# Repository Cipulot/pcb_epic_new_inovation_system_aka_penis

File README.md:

# pcb_epic_new_inovation_system_aka_penis
Do NOT use this in any comercial way ,all the files may not be used to gain any profit. Retail of these designs is not allowed by anyone else then the creator. Also dont complain about the PCB.

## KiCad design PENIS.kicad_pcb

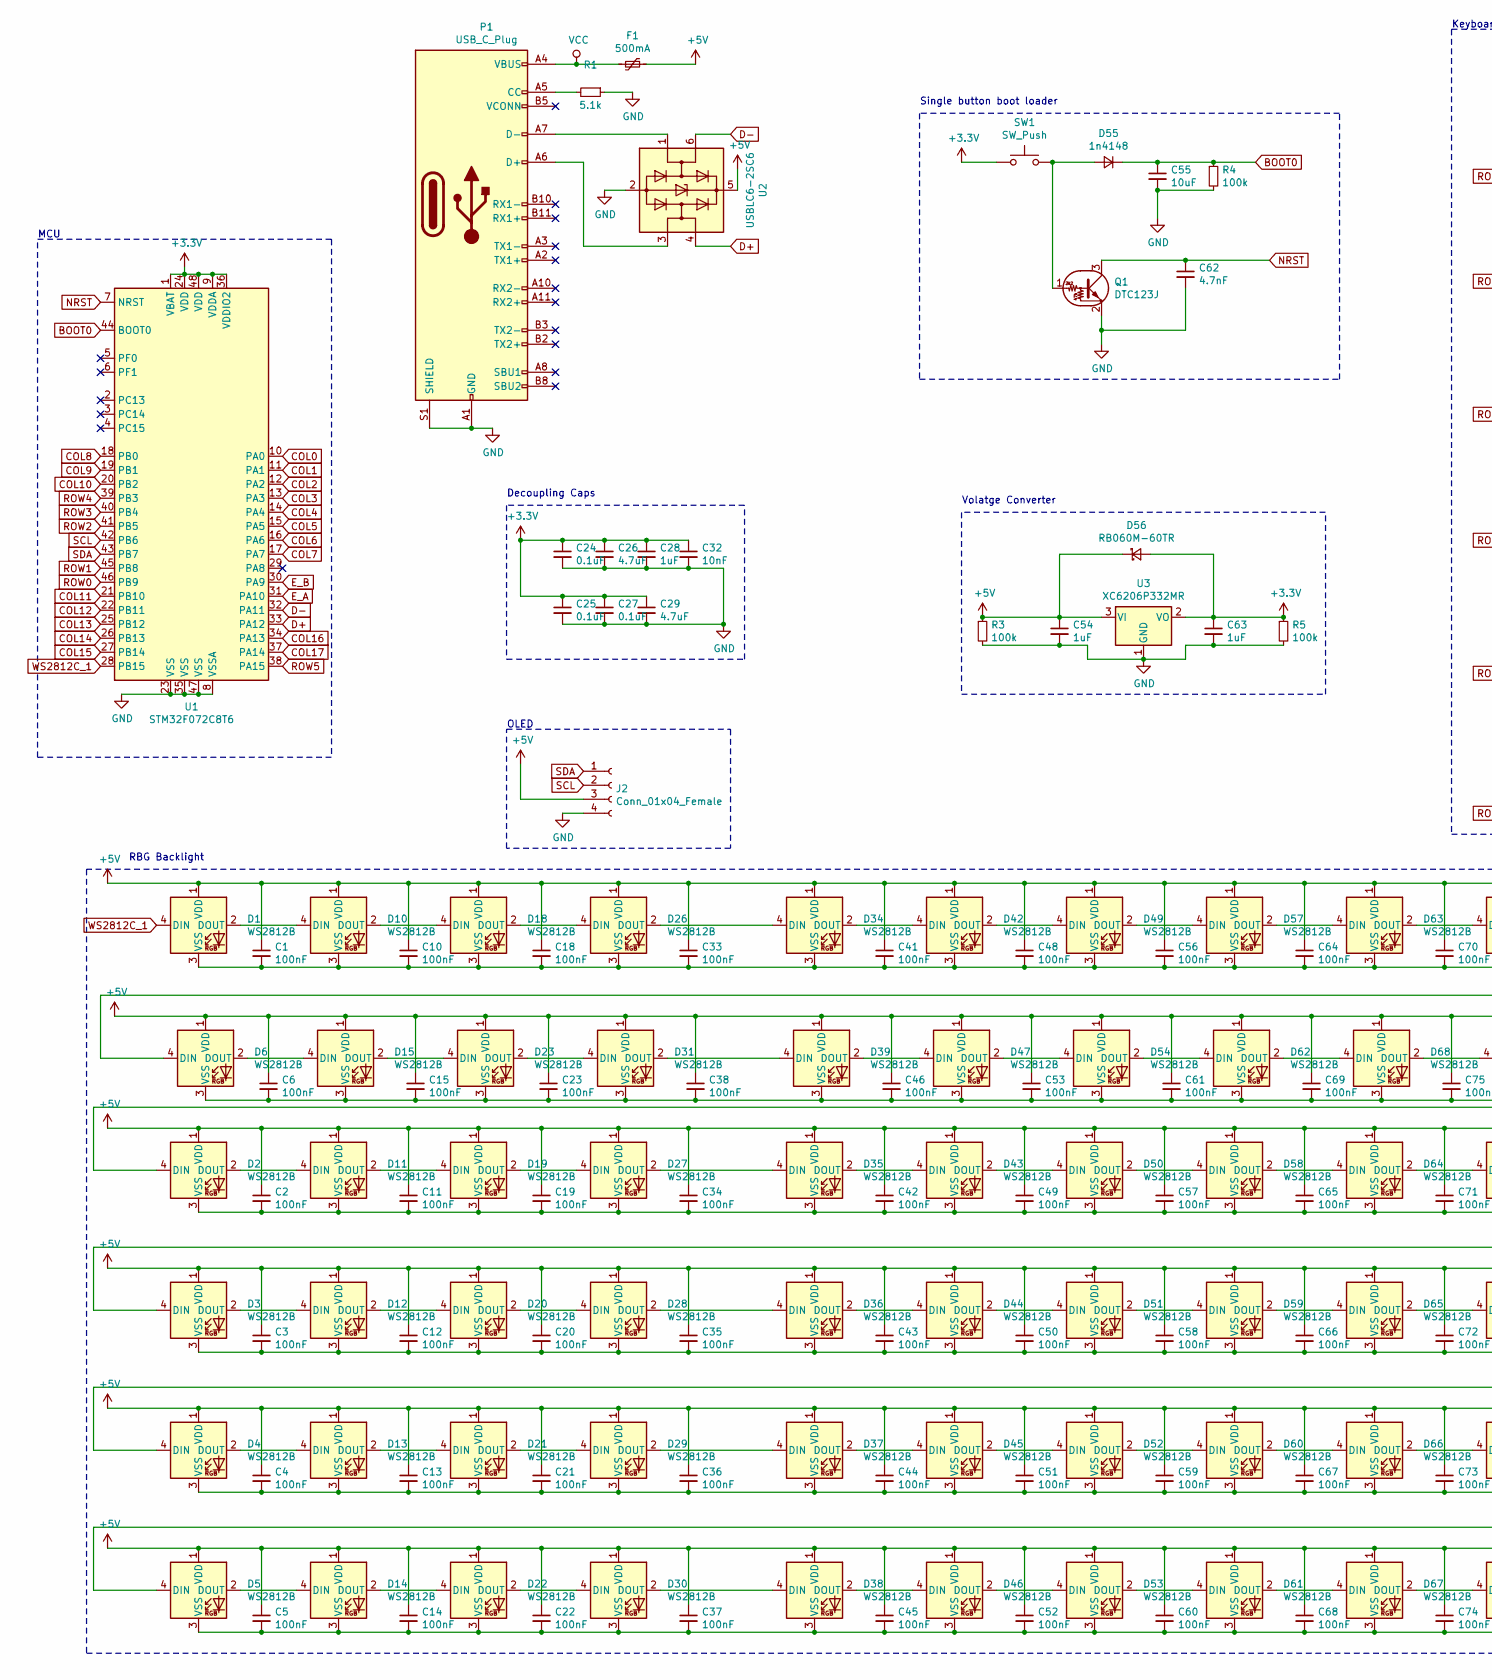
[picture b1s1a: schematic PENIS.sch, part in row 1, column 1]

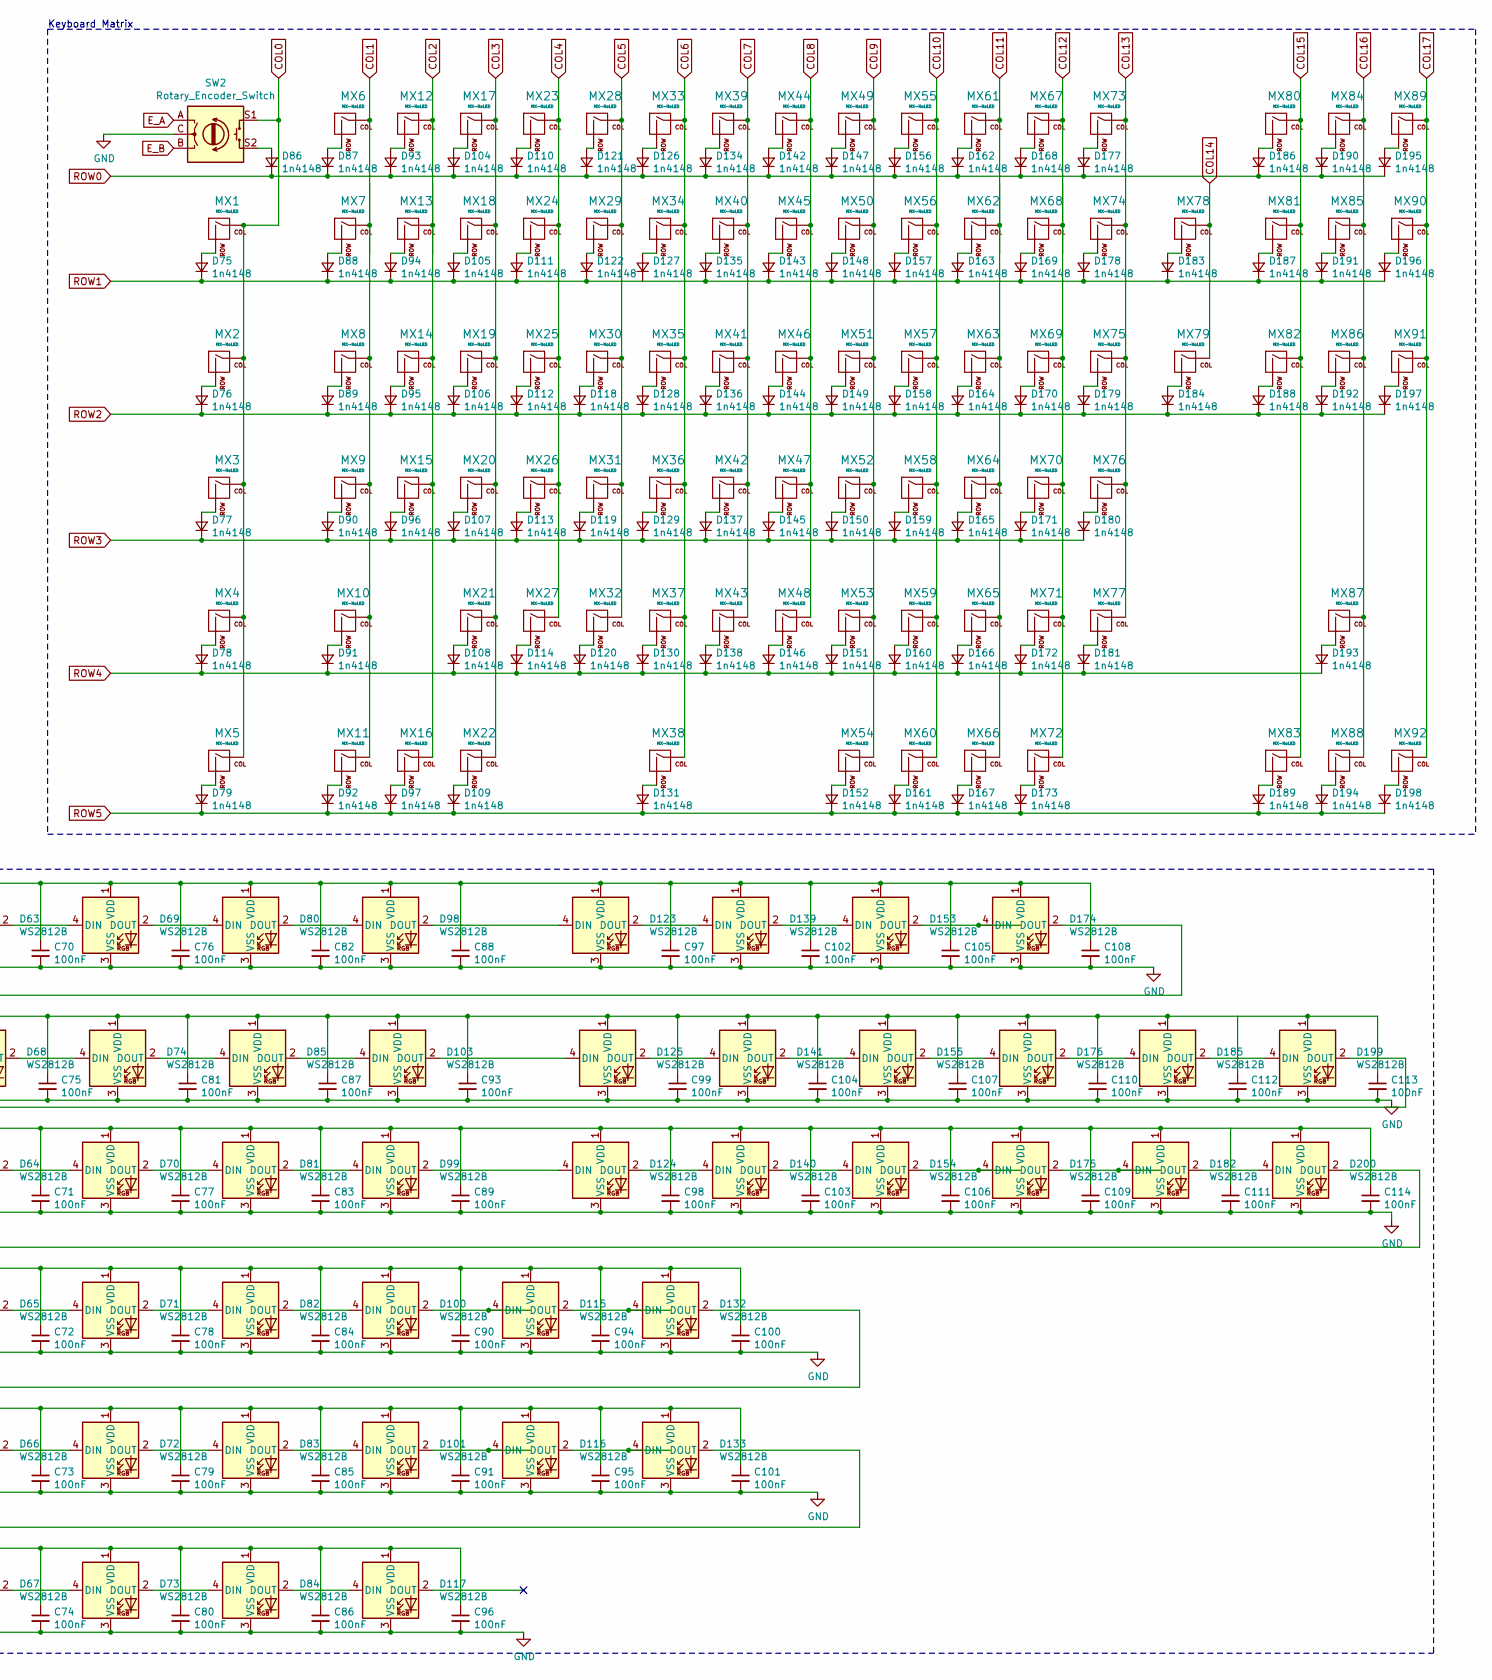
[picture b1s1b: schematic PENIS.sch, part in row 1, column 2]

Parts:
C1, C2, C3, C4, C5, C6, C10, C11, C12, C13, C14, C15, C18, C19, C20, C21, C22, C23, C33, C34, C35, C36, C37, C38, C41, C42, C43, C44, C45, C46, C48, C49, C50, C51, C52, C53, C56, C57, C58, C59, C60, C61, C64, C65, C66, C67, C68, C69, C70, C71, C72, C73, C74, C75, C76, C77, C78, C79, C80, C81, C82, C83, C84, C85, C86, C87, C88, C89, C90, C91, C93, C94, C95, C96, C97, C98, C99, C100, C101, C102, C103, C104, C105, C106, C107, C108, C109, C110, C111, C112, C113, C114: 100nF; C_0805_2012Metric
C24, C25, C27: 0.1uF; C_0805_2012Metric
C26, C29: 4.7uF; C_0805_2012Metric
C28, C54, C63: 1uF; C_0805_2012Metric
C32: 10nF; C_0805_2012Metric
C55: 10uF; C_0805_2012Metric
C62: 4.7nF; C_0805_2012Metric
D1, D2, D3, D4, D5, D6, D10, D11, D12, D13, D14, D15, D18, D19, D20, D21, D22, D23, D26, D27, D28, D29, D30, D31, D34, D35, D36, D37, D38, D39, D42, D43, D44, D45, D46, D47, D49, D50, D51, D52, D53, D54, D57, D58, D59, D60, D61, D62, D63, D64, D65, D66, D67, D68, D69, D70, D71, D72, D73, D74, D80, D81, D82, D83, D84, D85, D98, D99, D100, D101, D103, D115, D116, D117, D123, D124, D125, D132, D133, D139, D140, D141, D153, D154, D155, D174, D175, D176, D182, D185, D199, D200: WS2812B; SK6812MINIE
D55, D75, D76, D77, D78, D79, D86, D87, D88, D89, D90, D91, D92, D93, D94, D95, D96, D97, D104, D105, D106, D107, D108, D109, D110, D111, D112, D113, D114, D118, D119, D120, D121, D122, D126, D127, D128, D129, D130, D131, D134, D135, D136, D137, D138, D142, D143, D144, D145, D146, D147, D148, D149, D150, D151, D152, D156, D157, D158, D159, D160, D161, D162, D163, D164, D165, D166, D167, D168, D169, D170, D171, D172, D173, D177, D178, D179, D180, D181, D183, D184, D186, D187, D188, D189, D190, D191, D192, D193, D194, D195, D196, D197, D198: 1n4148; D_DO-35_SOD27_P10.16mm_Horizontal
D56: RB060M-60TR; D_SOD-123
F1: 500mA; Fuse_1206_3216Metric
J2: Conn_01x04_Female; PinSocket_1x04_P2.54mm_Vertical
MX1, MX2, MX3, MX4, MX5, MX6, MX7, MX12, MX13, MX14, MX15, MX17, MX18, MX19, MX20, MX21, MX23, MX24, MX25, MX26, MX27, MX28, MX29, MX30, MX31, MX32, MX33, MX34, MX35, MX36, MX37, MX39, MX40, MX41, MX42, MX43, MX44, MX45, MX46, MX47, MX48, MX49, MX50, MX51, MX52, MX53, MX55, MX56, MX57, MX58, MX59, MX61, MX62, MX63, MX64, MX65, MX67, MX68, MX69, MX70, MX71, MX73, MX74, MX75, MX80, MX81, MX82, MX83, MX84, MX85, MX86, MX87, MX88, MX89, MX90, MX91, MX92: MX-NoLED; MXOnly-1U-Hotswap
MX8, MX79: MX-NoLED; MXOnly-1.5U-Hotswap
MX9: MX-NoLED; MXOnly-1.75U-Hotswap
MX10, MX76: MX-NoLED; MXOnly-2.25U-Hotswap
MX11, MX16, MX22, MX54, MX60, MX66, MX72: MX-NoLED; MXOnly-1.25U-Hotswap
MX38: MX-NoLED; MXOnly-6.25U-Hotswap
MX77: MX-NoLED; MXOnly-2.75U-Hotswap
MX78: MX-NoLED; MXOnly-2U-Hotswap
P1: USB_C_Plug; USB_C_Receptacle_HRO_TYPE-C-31-M-12
Q1: DTC123J; SOT23-3_HSOL
R1: 5.1k; R_0805_2012Metric
R3, R4, R5: 100k; R_0805_2012Metric
SW1: SW_Push; SW_PUSH_6mm
SW2: Rotary_Encoder_Switch; RotaryEncoder_Alps_EC11E-Switch_Vertical_H20mm
U1: STM32F072C8T6; LQFP-48_7x7mm_P0.5mm
U2: USBLC6-2SC6; SOT-23-6
U3: XC6206P332MR; SOT-23

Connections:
+3V3: C24.1, C25.1, C26.1, C27.1, C28.1, C29.1, C32.1, C63.1, D56.2 (A), R5.1, SW1.1, U1.1 (VBAT), U1.9 (VDDA), U1.24 (VDD), U1.36 (VDDIO2), U1.48 (VDD), U3.2 (VO)
+5V: C1.1, C2.1, C3.1, C4.1, C5.1, C6.1, C10.1, C11.1, C12.1, C13.1, C14.1, C15.1, C18.1, C19.1, C20.1, C21.1, C22.1, C23.1, C33.1, C34.1, C35.1, C36.1, C37.1, C38.1, C41.1, C42.1, C43.1, C44.1, C45.1, C46.1, C48.1, C49.1, C50.1, C51.1, C52.1, C53.1, C54.1, C56.1, C57.1, C58.1, C59.1, C60.1, C61.1, C64.1, C65.1, C66.1, C67.1, C68.1, C69.1, C70.1, C71.1, C72.1, C73.1, C74.1, C75.1, C76.1, C77.1, C78.1, C79.1, C80.1, C81.1, C82.1, C83.1, C84.1, C85.1, C86.1, C87.1, C88.1, C89.1, C90.1, C91.1, C93.1, C94.1, C95.1, C96.1, C97.1, C98.1, C99.1, C100.1, C101.1, C102.1, C103.1, C104.1, C105.1, C106.1, C107.1, C108.1, C109.1, C110.1, C111.1, C112.1, C113.1, C114.1, D1.1 (VDD), D2.1 (VDD), D3.1 (VDD), D4.1 (VDD), D5.1 (VDD), D6.1 (VDD), D10.1 (VDD), D11.1 (VDD), D12.1 (VDD), D13.1 (VDD), D14.1 (VDD), D15.1 (VDD), D18.1 (VDD), D19.1 (VDD), D20.1 (VDD), D21.1 (VDD), D22.1 (VDD), D23.1 (VDD), D26.1 (VDD), D27.1 (VDD), D28.1 (VDD), D29.1 (VDD), D30.1 (VDD), D31.1 (VDD), D34.1 (VDD), D35.1 (VDD), D36.1 (VDD), D37.1 (VDD), D38.1 (VDD), D39.1 (VDD), D42.1 (VDD), D43.1 (VDD), D44.1 (VDD), D45.1 (VDD), D46.1 (VDD), D47.1 (VDD), D49.1 (VDD), D50.1 (VDD), D51.1 (VDD), D52.1 (VDD), D53.1 (VDD), D54.1 (VDD), D56.1 (K), D57.1 (VDD), D58.1 (VDD), D59.1 (VDD), D60.1 (VDD), D61.1 (VDD), D62.1 (VDD), D63.1 (VDD), D64.1 (VDD), D65.1 (VDD), D66.1 (VDD), D67.1 (VDD), D68.1 (VDD), D69.1 (VDD), D70.1 (VDD), D71.1 (VDD), D72.1 (VDD), D73.1 (VDD), D74.1 (VDD), D80.1 (VDD), D81.1 (VDD), D82.1 (VDD), D83.1 (VDD), D84.1 (VDD), D85.1 (VDD), D98.1 (VDD), D99.1 (VDD), D100.1 (VDD), D101.1 (VDD), D103.1 (VDD), D115.1 (VDD), D116.1 (VDD), D117.1 (VDD), D123.1 (VDD), D124.1 (VDD), D125.1 (VDD), D132.1 (VDD), D133.1 (VDD), D139.1 (VDD), D140.1 (VDD), D141.1 (VDD), D153.1 (VDD), D154.1 (VDD), D155.1 (VDD), D174.1 (VDD), D175.1 (VDD), D176.1 (VDD), D182.1 (VDD), D185.1 (VDD), D199.1 (VDD), D200.1 (VDD), F1.1, J2.3, R3.1, U2.5 (VBUS), U3.3 (VI)
BOOT0: C55.1, D55.1 (K), R4.1, U1.44 (BOOT0)
COL0: MX1.1 (COL), MX2.1 (COL), MX3.1 (COL), MX4.1 (COL), MX5.1 (COL), SW2.S1, U1.10 (PA0)
COL1: MX6.1 (COL), MX7.1 (COL), MX8.1 (COL), MX9.1 (COL), MX10.1 (COL), MX11.1 (COL), U1.11 (PA1)
COL2: MX12.1 (COL), MX13.1 (COL), MX14.1 (COL), MX15.1 (COL), MX16.1 (COL), U1.12 (PA2)
COL3: MX17.1 (COL), MX18.1 (COL), MX19.1 (COL), MX20.1 (COL), MX21.1 (COL), MX22.1 (COL), U1.13 (PA3)
COL4: MX23.1 (COL), MX24.1 (COL), MX25.1 (COL), MX26.1 (COL), MX27.1 (COL), U1.14 (PA4)
COL5: MX28.1 (COL), MX29.1 (COL), MX30.1 (COL), MX31.1 (COL), MX32.1 (COL), U1.15 (PA5)
COL6: MX33.1 (COL), MX34.1 (COL), MX35.1 (COL), MX36.1 (COL), MX37.1 (COL), MX38.1 (COL), U1.16 (PA6)
COL7: MX39.1 (COL), MX40.1 (COL), MX41.1 (COL), MX42.1 (COL), MX43.1 (COL), U1.17 (PA7)
COL8: MX44.1 (COL), MX45.1 (COL), MX46.1 (COL), MX47.1 (COL), MX48.1 (COL), U1.18 (PB0)
COL9: MX49.1 (COL), MX50.1 (COL), MX51.1 (COL), MX52.1 (COL), MX53.1 (COL), MX54.1 (COL), U1.19 (PB1)
COL10: MX55.1 (COL), MX56.1 (COL), MX57.1 (COL), MX58.1 (COL), MX59.1 (COL), MX60.1 (COL), U1.20 (PB2)
COL11: MX61.1 (COL), MX62.1 (COL), MX63.1 (COL), MX64.1 (COL), MX65.1 (COL), MX66.1 (COL), U1.21 (PB10)
COL12: MX67.1 (COL), MX68.1 (COL), MX69.1 (COL), MX70.1 (COL), MX71.1 (COL), MX72.1 (COL), U1.22 (PB11)
COL13: MX73.1 (COL), MX74.1 (COL), MX75.1 (COL), MX76.1 (COL), MX77.1 (COL), U1.25 (PB12)
COL14: MX78.1 (COL), MX79.1 (COL), U1.26 (PB13)
COL15: MX80.1 (COL), MX81.1 (COL), MX82.1 (COL), MX83.1 (COL), U1.27 (PB14)
COL16: MX84.1 (COL), MX85.1 (COL), MX86.1 (COL), MX87.1 (COL), MX88.1 (COL), U1.34 (PA13)
COL17: MX89.1 (COL), MX90.1 (COL), MX91.1 (COL), MX92.1 (COL), U1.37 (PA14)
D+: U1.33 (PA12), U2.4 (I/O2)
D-: U1.32 (PA11), U2.6 (I/O1)
E_A: SW2.A, U1.31 (PA10)
E_B: SW2.B, U1.30 (PA9)
GND: C1.2, C2.2, C3.2, C4.2, C5.2, C6.2, C10.2, C11.2, C12.2, C13.2, C14.2, C15.2, C18.2, C19.2, C20.2, C21.2, C22.2, C23.2, C24.2, C25.2, C26.2, C27.2, C28.2, C29.2, C32.2, C33.2, C34.2, C35.2, C36.2, C37.2, C38.2, C41.2, C42.2, C43.2, C44.2, C45.2, C46.2, C48.2, C49.2, C50.2, C51.2, C52.2, C53.2, C54.2, C55.2, C56.2, C57.2, C58.2, C59.2, C60.2, C61.2, C62.2, C63.2, C64.2, C65.2, C66.2, C67.2, C68.2, C69.2, C70.2, C71.2, C72.2, C73.2, C74.2, C75.2, C76.2, C77.2, C78.2, C79.2, C80.2, C81.2, C82.2, C83.2, C84.2, C85.2, C86.2, C87.2, C88.2, C89.2, C90.2, C91.2, C93.2, C94.2, C95.2, C96.2, C97.2, C98.2, C99.2, C100.2, C101.2, C102.2, C103.2, C104.2, C105.2, C106.2, C107.2, C108.2, C109.2, C110.2, C111.2, C112.2, C113.2, C114.2, D1.3 (VSS), D2.3 (VSS), D3.3 (VSS), D4.3 (VSS), D5.3 (VSS), D6.3 (VSS), D10.3 (VSS), D11.3 (VSS), D12.3 (VSS), D13.3 (VSS), D14.3 (VSS), D15.3 (VSS), D18.3 (VSS), D19.3 (VSS), D20.3 (VSS), D21.3 (VSS), D22.3 (VSS), D23.3 (VSS), D26.3 (VSS), D27.3 (VSS), D28.3 (VSS), D29.3 (VSS), D30.3 (VSS), D31.3 (VSS), D34.3 (VSS), D35.3 (VSS), D36.3 (VSS), D37.3 (VSS), D38.3 (VSS), D39.3 (VSS), D42.3 (VSS), D43.3 (VSS), D44.3 (VSS), D45.3 (VSS), D46.3 (VSS), D47.3 (VSS), D49.3 (VSS), D50.3 (VSS), D51.3 (VSS), D52.3 (VSS), D53.3 (VSS), D54.3 (VSS), D57.3 (VSS), D58.3 (VSS), D59.3 (VSS), D60.3 (VSS), D61.3 (VSS), D62.3 (VSS), D63.3 (VSS), D64.3 (VSS), D65.3 (VSS), D66.3 (VSS), D67.3 (VSS), D68.3 (VSS), D69.3 (VSS), D70.3 (VSS), D71.3 (VSS), D72.3 (VSS), D73.3 (VSS), D74.3 (VSS), D80.3 (VSS), D81.3 (VSS), D82.3 (VSS), D83.3 (VSS), D84.3 (VSS), D85.3 (VSS), D98.3 (VSS), D99.3 (VSS), D100.3 (VSS), D101.3 (VSS), D103.3 (VSS), D115.3 (VSS), D116.3 (VSS), D117.3 (VSS), D123.3 (VSS), D124.3 (VSS), D125.3 (VSS), D132.3 (VSS), D133.3 (VSS), D139.3 (VSS), D140.3 (VSS), D141.3 (VSS), D153.3 (VSS), D154.3 (VSS), D155.3 (VSS), D174.3 (VSS), D175.3 (VSS), D176.3 (VSS), D182.3 (VSS), D185.3 (VSS), D199.3 (VSS), D200.3 (VSS), J2.4, P1.A1 (GND), P1.A12 (GND), P1.B1 (GND), P1.B12 (GND), P1.S1 (SHIELD), Q1.2 (E), R1.1, R3.2, R4.2, R5.2, SW2.C, U1.8 (VSSA), U1.23 (VSS), U1.35 (VSS), U1.47 (VSS), U2.2 (GND), U3.1 (GND)
NRST: C62.1, Q1.3 (C), U1.7 (NRST)
unnamed: D1.2 (DOUT), D10.4 (DIN)
unnamed: D10.2 (DOUT), D18.4 (DIN)
unnamed: D11.2 (DOUT), D19.4 (DIN)
unnamed: D2.2 (DOUT), D11.4 (DIN)
unnamed: D12.2 (DOUT), D20.4 (DIN)
unnamed: D3.2 (DOUT), D12.4 (DIN)
unnamed: D13.2 (DOUT), D21.4 (DIN)
unnamed: D4.2 (DOUT), D13.4 (DIN)
unnamed: D14.2 (DOUT), D22.4 (DIN)
unnamed: D5.2 (DOUT), D14.4 (DIN)
unnamed: D15.2 (DOUT), D23.4 (DIN)
unnamed: D6.2 (DOUT), D15.4 (DIN)
unnamed: D18.2 (DOUT), D26.4 (DIN)
unnamed: D19.2 (DOUT), D27.4 (DIN)
unnamed: D20.2 (DOUT), D28.4 (DIN)
unnamed: D21.2 (DOUT), D29.4 (DIN)
unnamed: D22.2 (DOUT), D30.4 (DIN)
unnamed: D23.2 (DOUT), D31.4 (DIN)
unnamed: D26.2 (DOUT), D34.4 (DIN)
unnamed: D27.2 (DOUT), D35.4 (DIN)
unnamed: D28.2 (DOUT), D36.4 (DIN)
unnamed: D29.2 (DOUT), D37.4 (DIN)
unnamed: D30.2 (DOUT), D38.4 (DIN)
unnamed: D31.2 (DOUT), D39.4 (DIN)
unnamed: D34.2 (DOUT), D42.4 (DIN)
unnamed: D35.2 (DOUT), D43.4 (DIN)
unnamed: D36.2 (DOUT), D44.4 (DIN)
unnamed: D37.2 (DOUT), D45.4 (DIN)
unnamed: D38.2 (DOUT), D46.4 (DIN)
unnamed: D39.2 (DOUT), D47.4 (DIN)
unnamed: D42.2 (DOUT), D49.4 (DIN)
unnamed: D43.2 (DOUT), D50.4 (DIN)
unnamed: D44.2 (DOUT), D51.4 (DIN)
unnamed: D45.2 (DOUT), D52.4 (DIN)
unnamed: D46.2 (DOUT), D53.4 (DIN)
unnamed: D47.2 (DOUT), D54.4 (DIN)
unnamed: D49.2 (DOUT), D57.4 (DIN)
unnamed: D50.2 (DOUT), D58.4 (DIN)
unnamed: D51.2 (DOUT), D59.4 (DIN)
unnamed: D52.2 (DOUT), D60.4 (DIN)
unnamed: D53.2 (DOUT), D61.4 (DIN)
unnamed: D54.2 (DOUT), D62.4 (DIN)
unnamed: D55.2 (A), Q1.1 (B), SW1.2
unnamed: D57.2 (DOUT), D63.4 (DIN)
unnamed: D58.2 (DOUT), D64.4 (DIN)
unnamed: D59.2 (DOUT), D65.4 (DIN)
unnamed: D60.2 (DOUT), D66.4 (DIN)
unnamed: D61.2 (DOUT), D67.4 (DIN)
unnamed: D62.2 (DOUT), D68.4 (DIN)
unnamed: D63.2 (DOUT), D69.4 (DIN)
unnamed: D64.2 (DOUT), D70.4 (DIN)
unnamed: D65.2 (DOUT), D71.4 (DIN)
unnamed: D66.2 (DOUT), D72.4 (DIN)
unnamed: D67.2 (DOUT), D73.4 (DIN)
unnamed: D68.2 (DOUT), D74.4 (DIN)
unnamed: D69.2 (DOUT), D80.4 (DIN)
unnamed: D70.2 (DOUT), D81.4 (DIN)
unnamed: D71.2 (DOUT), D82.4 (DIN)
unnamed: D72.2 (DOUT), D83.4 (DIN)
unnamed: D73.2 (DOUT), D84.4 (DIN)
unnamed: D74.2 (DOUT), D85.4 (DIN)
unnamed: D75.2 (A), MX1.2 (ROW)
unnamed: D76.2 (A), MX2.2 (ROW)
unnamed: D77.2 (A), MX3.2 (ROW)
unnamed: D78.2 (A), MX4.2 (ROW)
unnamed: D79.2 (A), MX5.2 (ROW)
unnamed: D80.2 (DOUT), D98.4 (DIN)
unnamed: D81.2 (DOUT), D99.4 (DIN)
unnamed: D86.2 (A), SW2.S2
unnamed: D87.2 (A), MX6.2 (ROW)
unnamed: D88.2 (A), MX7.2 (ROW)
unnamed: D89.2 (A), MX8.2 (ROW)
unnamed: D90.2 (A), MX9.2 (ROW)
unnamed: D91.2 (A), MX10.2 (ROW)
unnamed: D92.2 (A), MX11.2 (ROW)
unnamed: D93.2 (A), MX12.2 (ROW)
unnamed: D94.2 (A), MX13.2 (ROW)
unnamed: D95.2 (A), MX14.2 (ROW)
unnamed: D96.2 (A), MX15.2 (ROW)
unnamed: D97.2 (A), MX16.2 (ROW)
unnamed: D100.2 (DOUT), D115.4 (DIN)
unnamed: D82.2 (DOUT), D100.4 (DIN)
unnamed: D101.2 (DOUT), D116.4 (DIN)
unnamed: D83.2 (DOUT), D101.4 (DIN)
unnamed: D103.2 (DOUT), D125.4 (DIN)
unnamed: D85.2 (DOUT), D103.4 (DIN)
unnamed: D104.2 (A), MX17.2 (ROW)
unnamed: D105.2 (A), MX18.2 (ROW)
unnamed: D106.2 (A), MX19.2 (ROW)
unnamed: D107.2 (A), MX20.2 (ROW)
unnamed: D108.2 (A), MX21.2 (ROW)
unnamed: D109.2 (A), MX22.2 (ROW)
unnamed: D110.2 (A), MX23.2 (ROW)
unnamed: D111.2 (A), MX24.2 (ROW)
unnamed: D112.2 (A), MX25.2 (ROW)
unnamed: D113.2 (A), MX26.2 (ROW)
unnamed: D114.2 (A), MX27.2 (ROW)
unnamed: D115.2 (DOUT), D132.4 (DIN)
unnamed: D116.2 (DOUT), D133.4 (DIN)
unnamed: D84.2 (DOUT), D117.4 (DIN)
unnamed: D118.2 (A), MX30.2 (ROW)
unnamed: D119.2 (A), MX31.2 (ROW)
unnamed: D120.2 (A), MX32.2 (ROW)
unnamed: D121.2 (A), MX28.2 (ROW)
unnamed: D122.2 (A), MX29.2 (ROW)
unnamed: D123.2 (DOUT), D139.4 (DIN)
unnamed: D98.2 (DOUT), D123.4 (DIN)
unnamed: D124.2 (DOUT), D140.4 (DIN)
unnamed: D99.2 (DOUT), D124.4 (DIN)
unnamed: D125.2 (DOUT), D141.4 (DIN)
unnamed: D126.2 (A), MX33.2 (ROW)
unnamed: D127.2 (A), MX34.2 (ROW)
unnamed: D128.2 (A), MX35.2 (ROW)
unnamed: D129.2 (A), MX36.2 (ROW)
unnamed: D130.2 (A), MX37.2 (ROW)
unnamed: D131.2 (A), MX38.2 (ROW)
unnamed: D4.4 (DIN), D132.2 (DOUT)
unnamed: D5.4 (DIN), D133.2 (DOUT)
unnamed: D134.2 (A), MX39.2 (ROW)
unnamed: D135.2 (A), MX40.2 (ROW)
unnamed: D136.2 (A), MX41.2 (ROW)
unnamed: D137.2 (A), MX42.2 (ROW)
unnamed: D138.2 (A), MX43.2 (ROW)
unnamed: D139.2 (DOUT), D153.4 (DIN)
unnamed: D140.2 (DOUT), D154.4 (DIN)
unnamed: D141.2 (DOUT), D155.4 (DIN)
unnamed: D142.2 (A), MX44.2 (ROW)
unnamed: D143.2 (A), MX45.2 (ROW)
unnamed: D144.2 (A), MX46.2 (ROW)
unnamed: D145.2 (A), MX47.2 (ROW)
unnamed: D146.2 (A), MX48.2 (ROW)
unnamed: D147.2 (A), MX49.2 (ROW)
unnamed: D148.2 (A), MX50.2 (ROW)
unnamed: D149.2 (A), MX51.2 (ROW)
unnamed: D150.2 (A), MX52.2 (ROW)
unnamed: D151.2 (A), MX53.2 (ROW)
unnamed: D152.2 (A), MX54.2 (ROW)
unnamed: D153.2 (DOUT), D174.4 (DIN)
unnamed: D154.2 (DOUT), D175.4 (DIN)
unnamed: D155.2 (DOUT), D176.4 (DIN)
unnamed: D156.2 (A), MX55.2 (ROW)
unnamed: D157.2 (A), MX56.2 (ROW)
unnamed: D158.2 (A), MX57.2 (ROW)
unnamed: D159.2 (A), MX58.2 (ROW)
unnamed: D160.2 (A), MX59.2 (ROW)
unnamed: D161.2 (A), MX60.2 (ROW)
unnamed: D162.2 (A), MX61.2 (ROW)
unnamed: D163.2 (A), MX62.2 (ROW)
unnamed: D164.2 (A), MX63.2 (ROW)
unnamed: D165.2 (A), MX64.2 (ROW)
unnamed: D166.2 (A), MX65.2 (ROW)
unnamed: D167.2 (A), MX66.2 (ROW)
unnamed: D168.2 (A), MX67.2 (ROW)
unnamed: D169.2 (A), MX68.2 (ROW)
unnamed: D170.2 (A), MX69.2 (ROW)
unnamed: D171.2 (A), MX70.2 (ROW)
unnamed: D172.2 (A), MX71.2 (ROW)
unnamed: D173.2 (A), MX72.2 (ROW)
unnamed: D6.4 (DIN), D174.2 (DOUT)
unnamed: D175.2 (DOUT), D182.4 (DIN)
unnamed: D176.2 (DOUT), D185.4 (DIN)
unnamed: D177.2 (A), MX73.2 (ROW)
unnamed: D178.2 (A), MX74.2 (ROW)
unnamed: D179.2 (A), MX75.2 (ROW)
unnamed: D180.2 (A), MX76.2 (ROW)
unnamed: D181.2 (A), MX77.2 (ROW)
unnamed: D182.2 (DOUT), D200.4 (DIN)
unnamed: D183.2 (A), MX78.2 (ROW)
unnamed: D184.2 (A), MX79.2 (ROW)
unnamed: D185.2 (DOUT), D199.4 (DIN)
unnamed: D186.2 (A), MX80.2 (ROW)
unnamed: D187.2 (A), MX81.2 (ROW)
unnamed: D188.2 (A), MX82.2 (ROW)
unnamed: D189.2 (A), MX83.2 (ROW)
unnamed: D190.2 (A), MX84.2 (ROW)
unnamed: D191.2 (A), MX85.2 (ROW)
unnamed: D192.2 (A), MX86.2 (ROW)
unnamed: D193.2 (A), MX87.2 (ROW)
unnamed: D194.2 (A), MX88.2 (ROW)
unnamed: D195.2 (A), MX89.2 (ROW)
unnamed: D196.2 (A), MX90.2 (ROW)
unnamed: D197.2 (A), MX91.2 (ROW)
unnamed: D198.2 (A), MX92.2 (ROW)
unnamed: D2.4 (DIN), D199.2 (DOUT)
unnamed: D3.4 (DIN), D200.2 (DOUT)
unnamed: P1.A5 (CC), R1.2
unnamed: P1.A6 (D+), U2.3 (I/O2)
unnamed: P1.A7 (D-), U2.1 (I/O1)
ROW0: D86.1 (K), D87.1 (K), D93.1 (K), D104.1 (K), D110.1 (K), D121.1 (K), D126.1 (K), D134.1 (K), D142.1 (K), D147.1 (K), D156.1 (K), D162.1 (K), D168.1 (K), D177.1 (K), D186.1 (K), D190.1 (K), D195.1 (K), U1.46 (PB9)
ROW1: D75.1 (K), D88.1 (K), D94.1 (K), D105.1 (K), D111.1 (K), D122.1 (K), D135.1 (K), D143.1 (K), D148.1 (K), D157.1 (K), D163.1 (K), D169.1 (K), D178.1 (K), D183.1 (K), D187.1 (K), D191.1 (K), D196.1 (K), U1.45 (PB8)
ROW2: D76.1 (K), D89.1 (K), D95.1 (K), D106.1 (K), D112.1 (K), D118.1 (K), D128.1 (K), D136.1 (K), D144.1 (K), D149.1 (K), D158.1 (K), D164.1 (K), D170.1 (K), D179.1 (K), D184.1 (K), D188.1 (K), D192.1 (K), D197.1 (K), U1.41 (PB5)
ROW3: D77.1 (K), D90.1 (K), D96.1 (K), D107.1 (K), D113.1 (K), D119.1 (K), D129.1 (K), D137.1 (K), D145.1 (K), D150.1 (K), D159.1 (K), D165.1 (K), D171.1 (K), D180.1 (K), U1.40 (PB4)
ROW4: D78.1 (K), D91.1 (K), D108.1 (K), D114.1 (K), D120.1 (K), D130.1 (K), D138.1 (K), D146.1 (K), D151.1 (K), D160.1 (K), D166.1 (K), D172.1 (K), D181.1 (K), D193.1 (K), U1.39 (PB3)
ROW5: D79.1 (K), D92.1 (K), D97.1 (K), D109.1 (K), D131.1 (K), D152.1 (K), D161.1 (K), D167.1 (K), D173.1 (K), D189.1 (K), D194.1 (K), D198.1 (K), U1.38 (PA15)
SCL: J2.2, U1.42 (PB6)
SDA: J2.1, U1.43 (PB7)
VCC: F1.2, P1.A4 (VBUS), P1.A9 (VBUS), P1.B4 (VBUS), P1.B9 (VBUS)
WS2812C_1: D1.4 (DIN), U1.28 (PB15)

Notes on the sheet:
Decoupling Caps
MCU
Single button boot loader
Volatge Converter
Keyboard Matrix
RBG Backlight
OLED

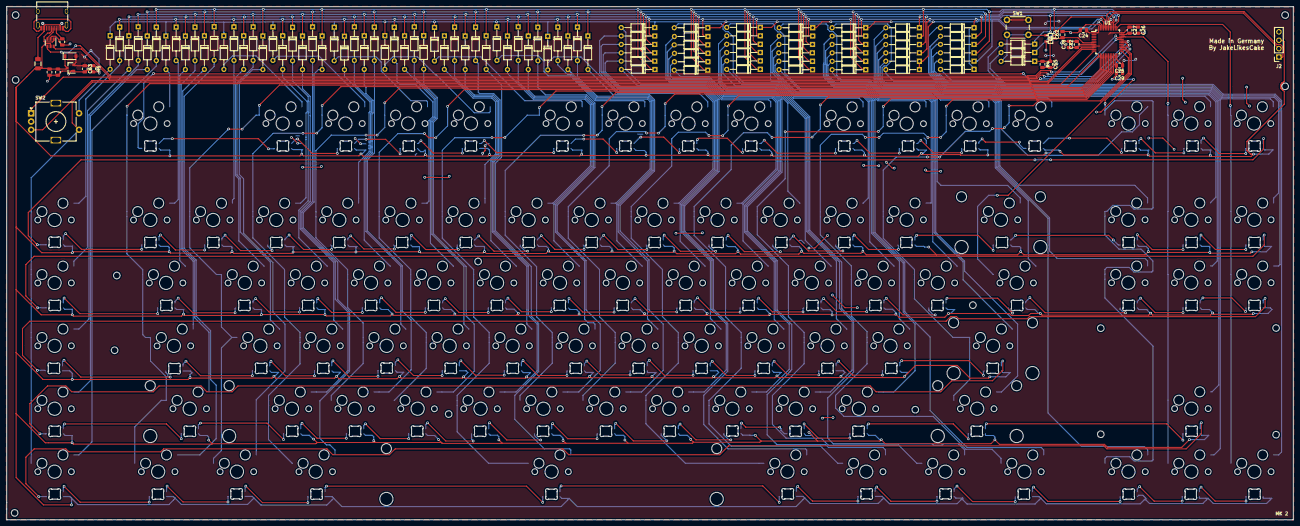
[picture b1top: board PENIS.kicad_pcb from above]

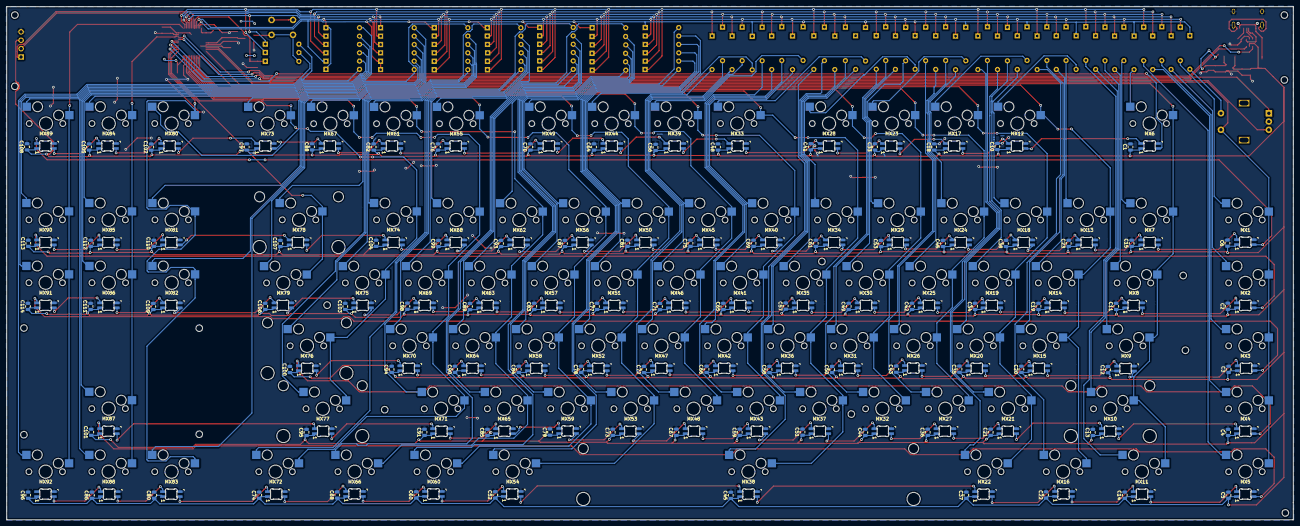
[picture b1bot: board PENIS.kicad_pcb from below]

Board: 2 copper layers, 389.5 x 155.3 mm, 395 parts (92 on the bottom side), 225 nets.

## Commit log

2020-07-15 Add submodules
2020-07-17 first schema
2020-08-17 MK2: dual layer and shittier in every other way
2020-08-17 Create LICENSE
    LICENSE bitches
2020-08-17 Mounting holes
2020-08-17 Gerber files
